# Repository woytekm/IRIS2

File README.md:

IRIS2 network radio project. This repository will contain all the necessary information required to build the unit.

Project images and video clips: https://drive.google.com/open?id=105BILNTAdYNRVomJvfbO0CPW3QA1uIXu

Currently we have here:
 - Code for core Iris application along with all necessary system scripts 
 - KiCad projects/schematics for all PCB's
 - STL's of all parts of the IRIS2 case
 - Some initial documentation
 
What we need to add:
 - More documentation
 - Detailed assembly instructions for all the PCB's and the unit itself
 - Detailed BOM for all of the PCB's, and additional stuff required to assemble the unit itself
 - Detailed instructions on how to make your own copy of IRIS2 firmware based on Raspbian (and/or firmware images)

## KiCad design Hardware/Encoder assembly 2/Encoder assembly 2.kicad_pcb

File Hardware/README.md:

This directory contains KiCad Projects of IRIS2 boards. Projects also contain Gerber files and schematics in PDF format.

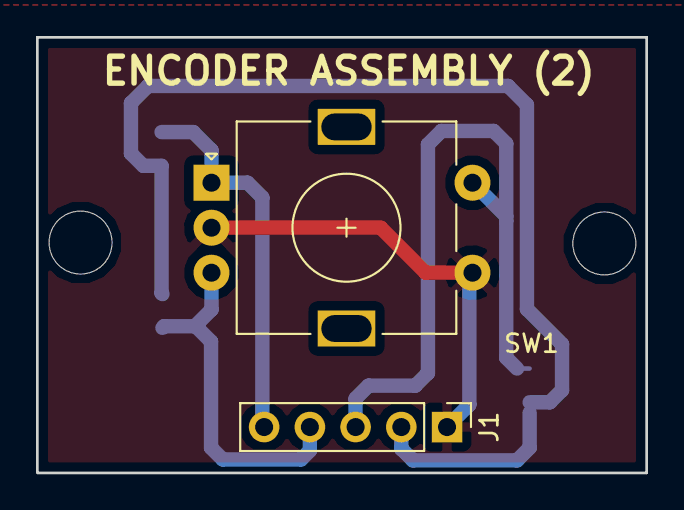
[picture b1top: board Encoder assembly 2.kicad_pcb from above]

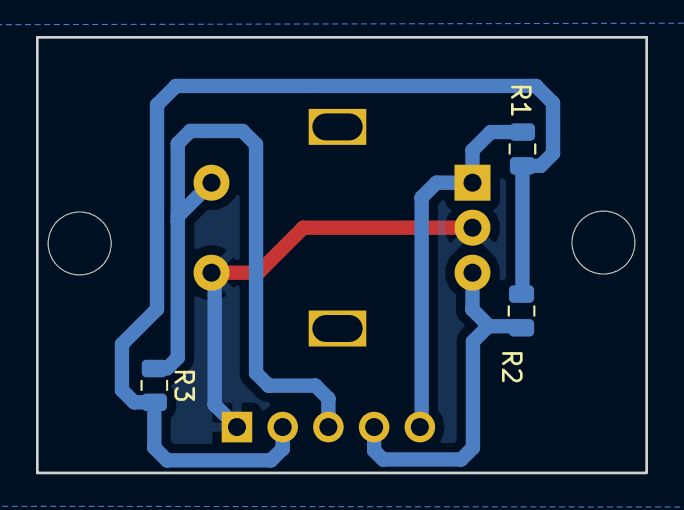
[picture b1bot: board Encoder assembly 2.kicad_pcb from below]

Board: 2 copper layers, 33.8 x 24.2 mm, 5 parts (3 on the bottom side), 5 nets.

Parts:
J1: Conn_01x05; PinHeader_1x05_P2.54mm_Vertical
R1, R2, R3: R_Small; R_0805_2012Metric
SW1: Rotary_Encoder_Switch; RotaryEncoder_Alps_EC11E-Switch_Vertical_H20mm

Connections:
+3V3: J1.2, R1.2, R2.2, R3.2
GND: J1.1, SW1.C, SW1.S1
unnamed: J1.3, R3.1, SW1.S2
unnamed: J1.4, R2.1, SW1.B
unnamed: J1.5, R1.1, SW1.A

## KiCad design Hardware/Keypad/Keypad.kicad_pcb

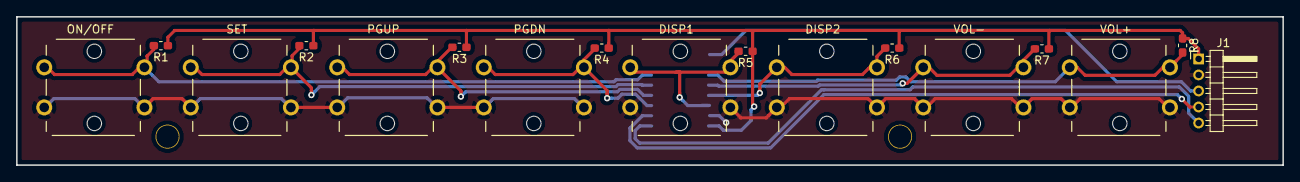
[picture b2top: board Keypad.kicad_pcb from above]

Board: 2 copper layers, 158.0 x 18.5 mm, 18 parts (1 on the bottom side), 13 nets.

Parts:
DISP1, DISP2: SW_Push_Dual; B3F-4050
J1: Conn_01x05; PinHeader_1x05_P2.00mm_Horizontal
ON/OFF: SW_Push_Dual; B3F-4050
PGDN: SW_Push_Dual; B3F-4050
PGUP: SW_Push_Dual; B3F-4050
R1, R2, R3, R4, R5, R6, R7, R8: R_Small; R_0603_1608Metric_Pad1.05x0.95mm_HandSolder
SET: SW_Push_Dual; B3F-4050
U1: 74LS165; SOIC-16W_5.3x10.2mm_P1.27mm
VOL+: SW_Push_Dual; B3F-4050
VOL-: SW_Push_Dual; B3F-4050

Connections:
+3V3: J1.1, R1.1, R2.1, R3.1, R4.1, R5.1, R6.1, R7.1, R8.1, U1.16
GND: DISP1.1, DISP1.3, DISP2.1, DISP2.3, J1.2, ON/OFF.1, ON/OFF.3, PGDN.1, PGDN.3, PGUP.1, PGUP.3, SET.1, SET.3, U1.8, U1.15, VOL+.1, VOL+.3, VOL-.1, VOL-.3
unnamed: J1.3, U1.9
unnamed: J1.4, U1.2
unnamed: J1.5, U1.1
unnamed: ON/OFF.2, ON/OFF.4, R1.2, U1.6
unnamed: R2.2, SET.2, SET.4, U1.5
unnamed: PGUP.2, PGUP.4, R3.2, U1.4
unnamed: PGDN.2, PGDN.4, R4.2, U1.3
unnamed: DISP1.2, DISP1.4, R5.2, U1.14
unnamed: DISP2.2, DISP2.4, R6.2, U1.13
unnamed: R7.2, U1.12, VOL-.2, VOL-.4
unnamed: R8.2, U1.11, VOL+.2, VOL+.4

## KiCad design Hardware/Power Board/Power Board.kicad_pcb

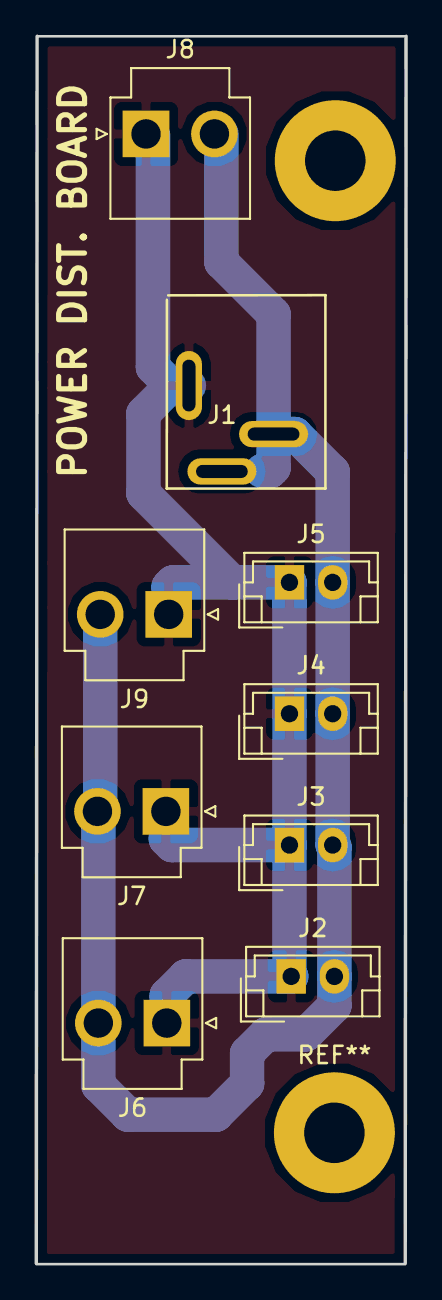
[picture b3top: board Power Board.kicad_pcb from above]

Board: 2 copper layers, 21.4 x 71.0 mm, 9 parts (0 on the bottom side), 2 nets.

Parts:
J1: Barrel_Jack_MountingPin; Barrel Jack Vertical
J2, J3, J4, J5: Conn_01x02; JST_EH_B02B-EH-A_1x02_P2.50mm_Vertical
J6, J7, J8, J9: Conn_01x02; JST_VH_B2P-VH-B_1x02_P3.96mm_Vertical

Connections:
unnamed: J1.1, J2.1, J3.1, J4.1, J5.1, J6.1, J7.1, J8.1, J9.1
unnamed: J1.2, J2.2, J3.2, J4.2, J5.2, J6.2, J7.2, J8.2, J9.2

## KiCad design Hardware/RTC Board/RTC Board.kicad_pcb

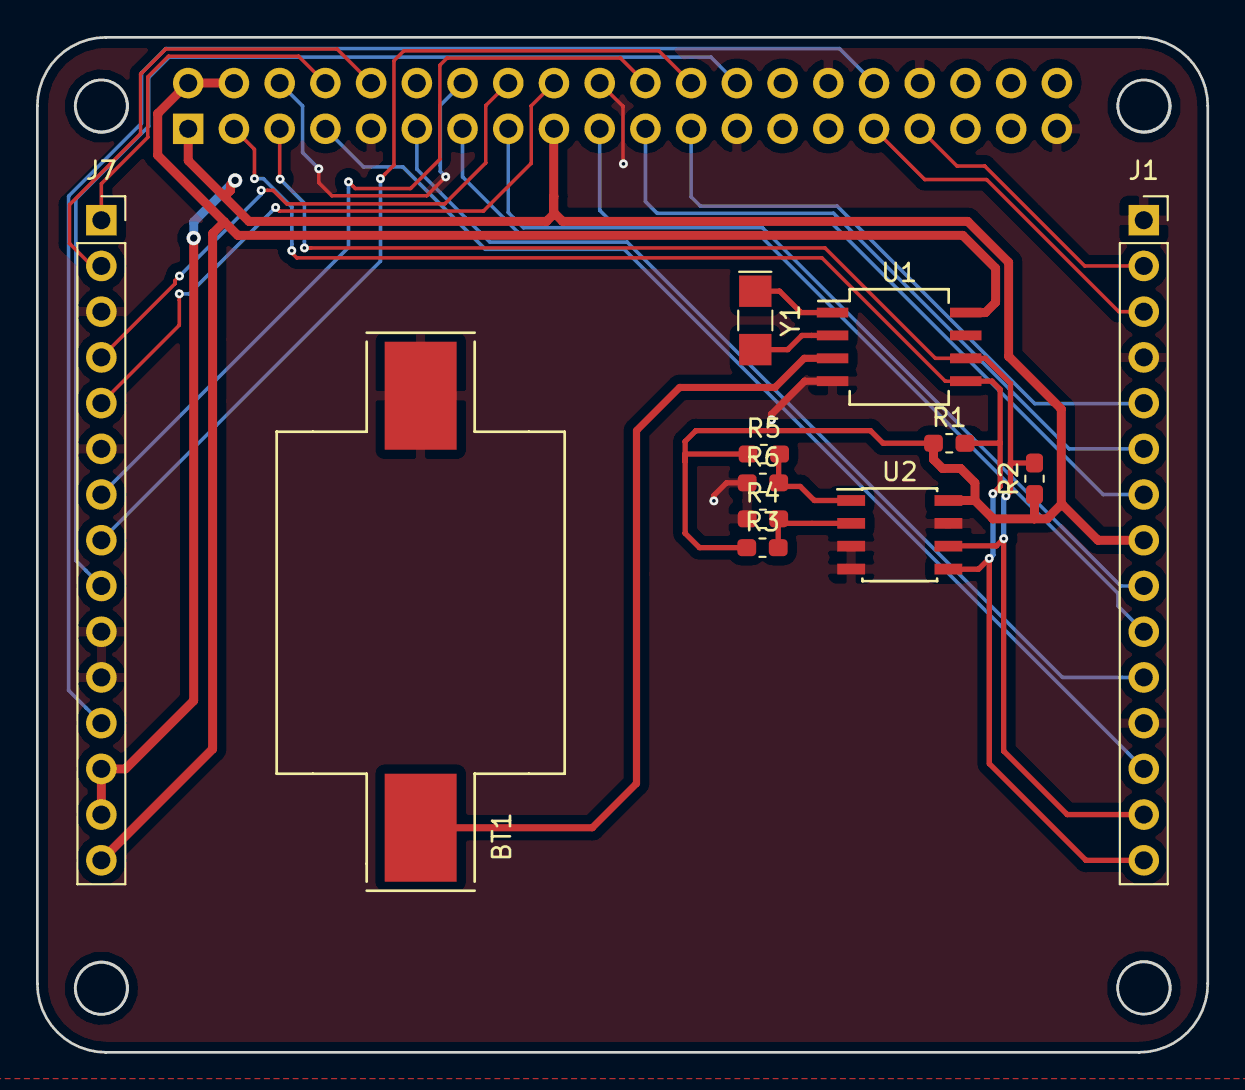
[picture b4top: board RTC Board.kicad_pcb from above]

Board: 2 copper layers, 65.0 x 56.4 mm, 13 parts (1 on the bottom side), 27 nets.

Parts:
BT1: Battery_Cell; CH29-CR2032
J1, J7: Conn_01x15; PinSocket_1x15_P2.54mm_Vertical
J6: Conn_02x20_Odd_Even; PinSocket_2x20_P2.54mm_Vertical
R1, R2: 1K; R_0603_1608Metric_Pad1.05x0.95mm_HandSolder
R3, R4, R5, R6: 0R; R_0603_1608Metric_Pad1.05x0.95mm_HandSolder
U1: DS1307Z+; SO-8_5.3x6.2mm_P1.27mm
U2: AT24C512; SOIC-8_3.9x4.9mm_P1.27mm
Y1: 32.768Kz; Crystal_SMD_G8-2Pin_3.2x1.5mm_HandSoldering

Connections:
+3V3: J1.8, J6.1, J6.17, J7.13, J7.14, R1.1, R2.1, R3.1, R5.1, U2.8
+5V_J4: J6.2, J6.4, J7.15, U1.8
GNDD: BT1.2, J1.1, J1.4, J1.12, J6.6, J6.9, J6.14, J6.20, J6.25, J6.30, J6.34, J6.39, J7.3, J7.6, J7.10, J7.11, R4.1, R6.1, U1.4, U2.3, U2.4, U2.7
H_SCL: J1.14, J6.5, R2.2, U1.6, U2.6
H_SDA: J1.15, J6.3, R1.2, U1.5, U2.5
unnamed: BT1.1, U1.3
unnamed: J1.2, J6.33
unnamed: J1.3, J6.31
unnamed: J1.5, J6.23
unnamed: J1.6, J6.21
unnamed: J1.7, J6.19
unnamed: J1.9, J6.15
unnamed: J1.10, J6.13
unnamed: J1.11, J6.11
unnamed: J1.13, J6.7
unnamed: J6.8, J7.1
unnamed: J6.10, J7.2
unnamed: J6.16, J7.4
unnamed: J6.18, J7.5
unnamed: J6.22, J7.7
unnamed: J6.24, J7.8
unnamed: J6.26, J7.9
unnamed: J6.32, J7.12
unnamed: R3.2, R4.2, U2.2
unnamed: R5.2, R6.2, U2.1
unnamed: U1.1, Y1.1
unnamed: U1.2, Y1.2

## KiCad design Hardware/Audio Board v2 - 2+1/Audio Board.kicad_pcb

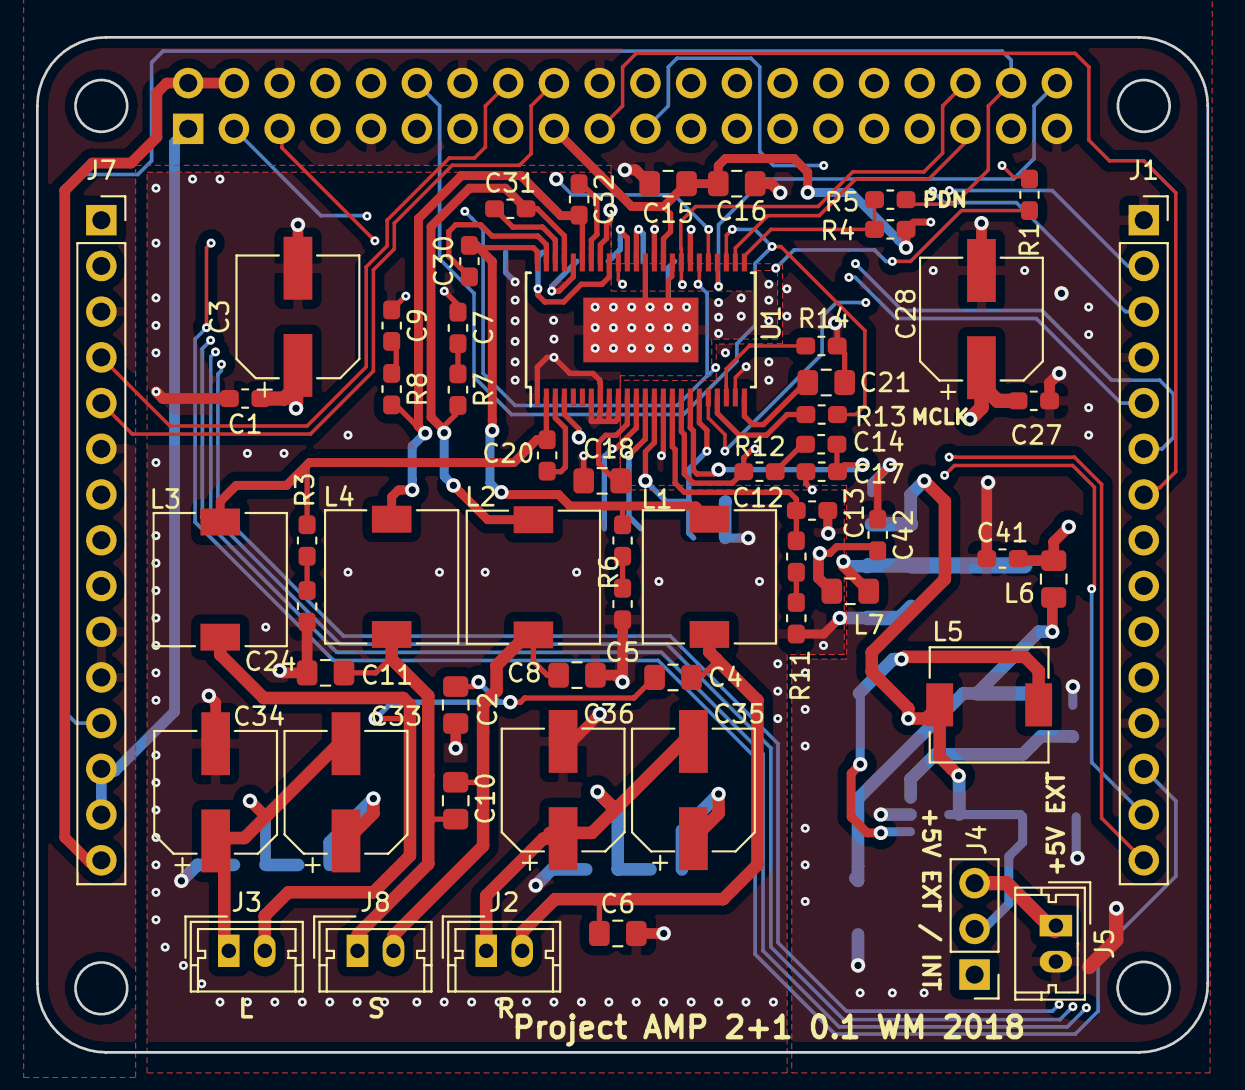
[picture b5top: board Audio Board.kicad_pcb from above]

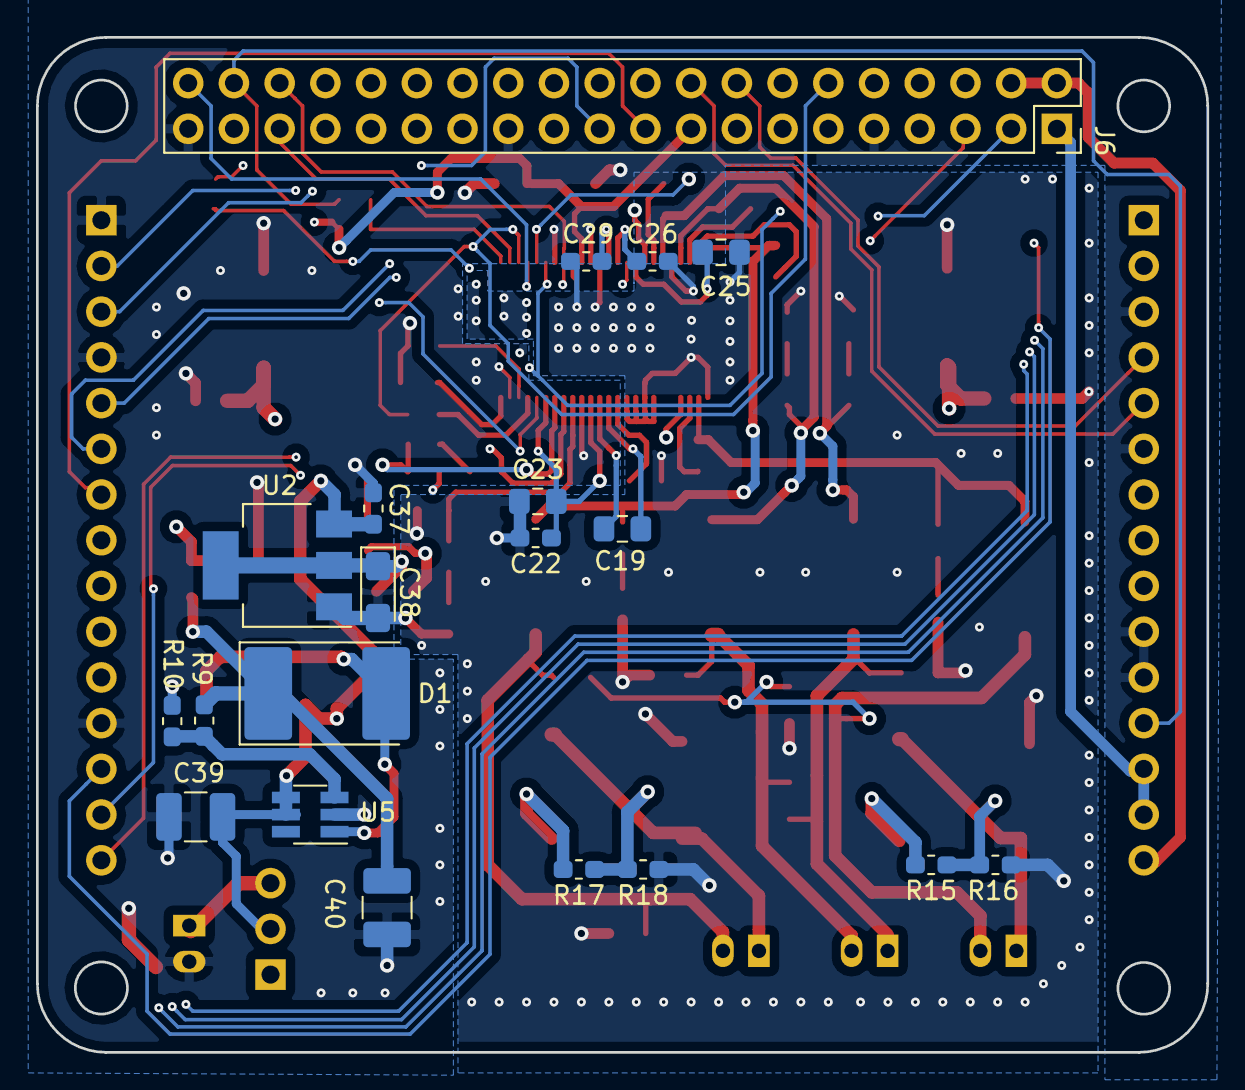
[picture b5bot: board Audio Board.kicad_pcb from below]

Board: 4 copper layers, 65.0 x 56.4 mm, 78 parts (20 on the bottom side), 70 nets.

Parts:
C1, C27: 0.1uF/25; C_0603_1608Metric_Pad1.05x0.95mm_HandSolder
C2, C4, C6, C8, C10, C11: 0.33uF/50; C_0805_2012Metric_Pad1.15x1.40mm_HandSolder
C3, C28: 220uF/25; CP_Elec_6.3x7.7
C5, C7, C9, C24: 330pF/50V; C_0603_1608Metric_Pad1.05x0.95mm_HandSolder
C12, C14: 0.047uF/16; C_0603_1608Metric_Pad1.05x0.95mm_HandSolder
C13, C17: 4700pF/25V; C_0603_1608Metric_Pad1.05x0.95mm_HandSolder
C15: 1uF/16; C_0805_2012Metric_Pad1.15x1.40mm_HandSolder
C16, C23: 10uF/16; C_0805_2012Metric_Pad1.15x1.40mm_HandSolder
C18, C19: 1uF/10; C_0805_2012Metric_Pad1.15x1.40mm_HandSolder
C20, C30, C31, C32: 0.033uF/50; C_0603_1608Metric_Pad1.05x0.95mm_HandSolder
C21: 4.7uF/6.3; C_0805_2012Metric_Pad1.15x1.40mm_HandSolder
C22: 100n/16; C_0603_1608Metric_Pad1.05x0.95mm_HandSolder
C25: 1uF/25V; C_0805_2012Metric_Pad1.15x1.40mm_HandSolder
C26: 2200pF/50V; C_0603_1608Metric_Pad1.05x0.95mm_HandSolder
C29: 0.1uF/16V; C_0603_1608Metric_Pad1.05x0.95mm_HandSolder
C33, C34, C35, C36: 220uF/50; CP_Elec_6.3x7.7
C37, C41, C42: 100nF/16; C_0603_1608Metric_Pad1.05x0.95mm_HandSolder
C38: 10uF/16; CP_EIA-3216-18_Kemet-A_Pad1.58x1.35mm_HandSolder
C39, C40: 22uF/25; C_1210_3225Metric_Pad1.42x2.65mm_HandSolder
D1: 10MQ040NTRPBF; D_3220_8050Metric_Pad2.65x5.15mm_HandSolder
J1, J7: Conn_01x15; PinSocket_1x15_P2.54mm_Vertical
J2, J3, J8: Conn_01x02; Molex_Micro-Latch_53253-0270_1x02_P2.00mm_Vertical
J4: Ext/Int +5V Analog; PinHeader_1x03_P2.54mm_Vertical
J5: +5V analog - external; Molex_Micro-Latch_53253-0270_1x02_P2.00mm_Vertical
J6: Conn_02x20_Odd_Even; PinSocket_2x20_P2.54mm_Vertical
L1, L2, L3, L4: 15uH/3.5A; L_7.3x7.3_H3.5
L5: 4.7uH 1A; L_6.3x6.3_H3
L6, L7: Ferrite Bead; L_0805_2012Metric_Pad1.15x1.40mm_HandSolder
R1, R5, R13: 0R; R_0603_1608Metric_Pad1.05x0.95mm_HandSolder
R3, R6, R7, R8: 18R; R_0603_1608Metric_Pad1.05x0.95mm_HandSolder
R4: 1K; R_0603_1608Metric_Pad1.05x0.95mm_HandSolder
R9: 3K; R_0603_1608Metric_Pad1.05x0.95mm_HandSolder
R10: 2.2K; R_0603_1608Metric_Pad1.05x0.95mm_HandSolder
R11, R12: 470R; R_0603_1608Metric_Pad1.05x0.95mm_HandSolder
R14: 18.2K; R_0603_1608Metric_Pad1.05x0.95mm_HandSolder
R15, R16, R17, R18: 15K; R_0603_1608Metric_Pad1.05x0.95mm_HandSolder
U1: TAS5721; HTSSOP48
U2: AP1117-33; SOT-223-3_TabPin2
U5: MT3608; SOT-23-6_Handsoldering

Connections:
+3.3VA: C22.1, C23.1, C42.2, L7.2, U1.14, U1.19
+3V3: C15.1, C16.1, J1.8, J6.1, J6.17, J7.13, J7.14, R4.1, U1.34
+5V: C37.2, C39.2, J4.2, L5.1, U2.3, U5.4, U5.5
+5V_J4: J4.1, J6.2, J6.4, J7.15
+12VA: C1.1, C3.1, C27.1, C28.1, C33.1, C35.1, C41.2, L6.2, R15.2, R17.2, U1.4, U1.41
GNDA: C1.2, C2.2, C3.2, C5.1, C6.2, C7.1, C8.2, C9.1, C11.2, C13.2, C15.2, C16.2, C18.2, C21.1, C22.2, C23.2, C24.1, C25.2, C26.2, C27.2, C28.2, C29.2, C34.2, C36.2, C37.1, C38.2, C39.1, C40.1, C41.1, C42.1, J1.1, J1.4, J1.12, J5.2, J6.6, J6.9, J6.14, J6.20, J6.25, J6.30, J6.34, J6.39, J7.3, J7.6, J7.10, J7.11, R10.1, R11.1, R14.2, R16.1, R18.1, U1.1, U1.7, U1.8, U1.9, U1.10, U1.15, U1.23, U1.31, U1.33, U1.35, U1.36, U1.44, U1.49, U2.1, U5.2
HEADER_FAULT: J6.32, U1.20
HEADER_I2S_BCK: J6.12, R13.2, U1.27
HEADER_I2S_DOUT: J6.40, U1.28
HEADER_I2S_LRCK: J6.35, U1.26
HEADER_PDN: J6.38, J7.12, R5.1
HEADER_RESET: J6.36, U1.32
H_SCL: J1.14, J6.5, U1.30
H_SDA: J1.15, J6.3, U1.29
MUTE: R1.1, U1.39
unnamed: C2.1, C4.1, J3.2, L3.2
unnamed: C4.2, C6.1, J2.2, L1.2
unnamed: C5.2, R6.1
unnamed: C7.2, R7.1
unnamed: C9.2, R8.1
unnamed: C8.1, C10.1, J8.2, L2.2
unnamed: C10.2, C11.1, J8.1, L4.2
unnamed: C12.1, C13.1, U1.16
unnamed: C12.2, R11.2
unnamed: C14.1, R12.1
unnamed: C14.2, C17.2, U1.18
unnamed: C17.1, R12.2, U1.17
unnamed: C18.1, U1.11
unnamed: C19.1, U1.12
unnamed: C19.2, U1.13
unnamed: C20.2, U1.3
unnamed: C21.2, U1.24
unnamed: C24.2, R3.1
unnamed: C25.1, U1.40
unnamed: C26.1, U1.38
unnamed: C29.1, U1.37
unnamed: C30.1, U1.47
unnamed: C31.1, U1.46
unnamed: C32.1, U1.42
unnamed: C38.1, L7.1, U2.2
unnamed: C40.2, D1.1, L6.1, R9.2
unnamed: D1.2, L5.2, U5.1
unnamed: J1.2, J6.33
unnamed: J1.3, J6.31
unnamed: J1.5, J6.23
unnamed: J1.6, J6.21
unnamed: J1.7, J6.19
unnamed: J1.9, J6.15
unnamed: J1.10, J6.13
unnamed: J1.11, J6.11
unnamed: J1.13, J6.7
unnamed: J4.3, J5.1
unnamed: J6.8, J7.1
unnamed: J6.10, J7.2
unnamed: J6.16, J7.4
unnamed: J6.18, J7.5
unnamed: J6.22, J7.7
unnamed: J6.24, J7.8
unnamed: J6.26, J7.9
unnamed: J6.37, R1.2
unnamed: R4.2, R5.2, U1.25
unnamed: R9.1, R10.2, U5.3
unnamed: R13.1, U1.21
unnamed: R14.1, U1.22
SPK_OUTA: C20.1, L3.1, R3.2, U1.2
SPK_OUTB: C30.2, L1.1, R6.2, U1.48
SPK_OUTC: C31.2, L2.1, R7.2, U1.45
SPK_OUTD: C32.2, L4.1, R8.2, U1.43
SPLIT_CAP_A: C33.2, C34.1, J3.1, R15.1, R16.2
SPLIT_CAP_B: C35.2, C36.1, J2.1, R17.1, R18.2

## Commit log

2018-12-02 Script initializing TAS5721 in 2.1 mode
2018-12-02 readme
2018-12-08 changes in TAS5721 init tool
2018-12-26 Commiting IRIS app source tree with modifications for new hardware components: AMP, matrix analyser, new keypad, etc... This is a start of IRIS2 main application development.
2018-12-26 version change for IRIS2 to 2.01
2018-12-27 - fixed makefile dependencies - adjusted keypad code to new keypad board with SN74165 parallel to serial shift register - moved main.c to separate dir - added system scripts required for building app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
2018-12-28 - fixed matrix bug (displaying frozen old FFT data when waiting for next stream to buffer) - moved matrix/fft to separate source file
2018-12-28 - started AMP/DAC abstraction layer
2019-01-15 bugfixes, cleanups, matrix clock, some other stuff
2019-02-07 Started bluetooth sink
2019-03-06 - fixed encoder bug - fixed matrix brightness bug - added matrix brightness setting - some BT stuff
2019-03-07 Started audio amplifier control abstraction layer and TAS5721 driver
2019-03-09 Amplifier control abstraction layer + TAS5721 driver (almost done)
2019-03-09 amplifier control
2019-03-12 added bluetooth helpers
2019-03-13 - fixed bluetooth sink bug - clock on matrix reactivated
2019-03-14 cleanups, small fixes
2019-04-21 - changed matrix clock font - added matrix color options - added alarm icon on matrix
2019-05-16 last changes before Maker Faire Berlin
2019-05-19 various small stuff done during Maker Faire Berlin
2019-05-19 config parsing bug fix and some config system improvements
2019-05-19 Added current STL files for the project
2019-05-19 Started adding project files for hardware
2019-05-19 cleaning up board projects
2019-05-19 Adding power distribution board project files
2019-05-19 Adding keypad board project files
2019-05-19 Adding documentation
2019-05-19 Adding rest of the boards
2019-05-19 Adding FPGA JIC file
2019-06-21 Added weather feature
2019-06-23 Added snow
2020-01-07 Some weather code changes which i've forgot to commit long time ago.
2020-01-07 don't use stream index from persistence if it's higher than loaded stream count
2020-09-30 Rapid API decided to start rip non commercial users off, so we are moving directly to querying Open Weather Map for weather
